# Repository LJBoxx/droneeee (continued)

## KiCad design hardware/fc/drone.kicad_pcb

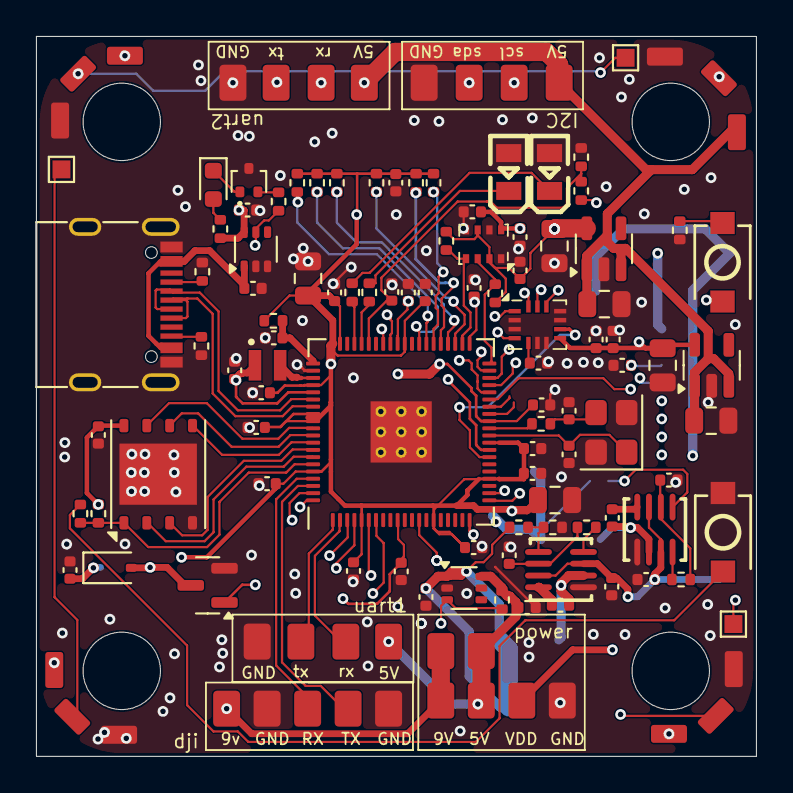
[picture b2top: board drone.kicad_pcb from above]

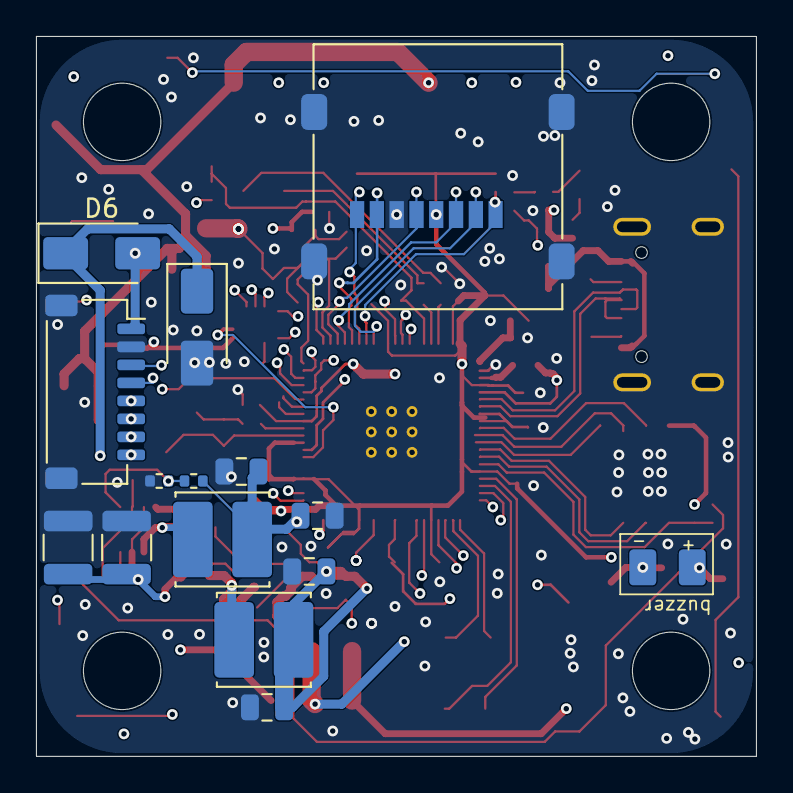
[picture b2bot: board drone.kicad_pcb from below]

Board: 4 copper layers, 40.0 x 40.0 mm, 137 parts (16 on the bottom side), 82 nets.

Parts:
C1, C4, C5, C6, C11, C12, C15, C16, C21, C22, C25, C26, C29, C35, C37, C38, C41, C42, C43, C45, C46, C49, C51: 100nf; C_0402_1005Metric
C2, C3, C7, C31: 4.7u; C_0402_1005Metric
C8, C17, C33: 100n; C_0402_1005Metric
C9, C10: 15p; C_0402_1005Metric
C13, C14, C23, C24: 1uf; C_0805_2012Metric
C18, C20, C30, C36: 22u; C_0805_2012Metric
C19, C34: 10u; C_1210_3225Metric
C27, C47: 2.2uf; C_0402_1005Metric
C28, C32, C39, C40: 1uf; C_0402_1005Metric
C44, C48: 10uf; C_0805_2012Metric
D1: C2297; LED0805-R-RD
D2: LED; LED_0603_1608Metric
D3: C2296; LED0805-R-RD
D4: D_Schottky; D_SOD-323
D6: D_Schottky; D_SMA
D8: SMAJ30A; D_SMA
J1, J3, J4, J5, J6, J7, J8, J9, J10, J11, J13, J14, J15, J16, J17, J18, J23, J24, J25, J26, J27, J28, J29: Conn_01x01; signal_pad
J2: Conn_01x08; JST_SH_SM08B-SRSS-TB_1x08-1MP_P1.00mm_Horizontal
J12: Micro_SD_Card; microSD_HC_Molex_47219-2001
J19, J20, J21, J22: Conn_01x03; led_ring
J30, J31, J32: Conn_01x01; TestPoint_Pad_1.0x1.0mm
L1, L2: 22uH; L_Cenker_CKCS5040
L3: 3.3u; L_pol_2016
Q1: AO3400A; SOT-23
Q2: NPN; SOT-416
R1, R2, R3, R4, R13, R20, R22, R23, R24, R27, R28, R29, R30: 10k; R_0402_1005Metric
R5, R7, R9, R10, R12: 100k; R_0402_1005Metric
R6, R14: 24.9k; R_0402_1005Metric
R8: 33r; R_0402_1005Metric
R11, R19, R21, R26: 1k; R_0402_1005Metric
R15, R16: 5.1k; R_0402_1005Metric
R25: 0; R_0402_1005Metric
SW1, SW2: SW_Push; SW-SMD_L3.9-W3.0-P4.45
TP1: BUZZER+; signal_pad
TP2: BUZZER-; signal_pad
U1, U7: MP9943GQ(TOKMAS); QFN-8_L3.0-W3.0-P0.65-BL
U2: TLV75533PDBV; SOT-23-5
U3: W25Q128JVP; WSON-8-1EP_6x5mm_P1.27mm_EP3.4x4.3mm
U4: RP2350_80QFN; RP2350-QFN-80-1EP_10x10_P0.4mm_EP3.4x3.4mm_ThermalVias
U5: ICM-42688-P; Bosch_LGA-14_3x2.5mm_P0.5mm
U6: LP5907MFX-3.3; SOT-23-5
U8: BMP280; Bosch_LGA-8_2x2.5mm_P0.65mm_ClockwisePinNumbering
U9, U10: LM66100DCK; SOT-363_SC-70-6
USB1: USB_C_Receptacle_USB2.0_14P; USB_C_Receptacle_G-Switch_GT-USB-7010ASV
Y1: ABM8-272-T3; Crystal_SMD_3225-4Pin_3.2x2.5mm

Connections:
+1V1: C2.1, C8.1, C11.2, C31.1, L3.1, U4.10 (DVDD), U4.32 (DVDD), U4.51 (DVDD), U4.65 (VREG_FB)
+5V: C14.1, C16.2, C23.2, C38.1, C41.1, D4.1 (K), J3.1 (Pin_1_1), J11.1 (Pin_1_1), J13.1 (Pin_1_1), J19.3, J20.3, J21.3, J22.3, J24.1 (Pin_1_1), J29.1 (Pin_1_1), R3.2, R11.1, TP1.1 (1_1), U2.1 (IN), U2.3 (EN), U6.1 (IN), U6.3 (EN), U9.6 (VOUT), U10.6 (VOUT)
+9V: C30.1, C36.1, J5.1 (Pin_1_1), J10.1 (Pin_1_1), J23.1 (Pin_1_1), L2.2, R9.2
/QSPI_SCLK: U3.6 (CLK), U4.71 (QSPI_SCLK)
/QSPI_SD0: U3.5 (DI/IO_{0}), U4.72 (QSPI_SD0)
/QSPI_SD1: U3.2 (DO/IO_{1}), U4.74 (QSPI_SD1)
/QSPI_SD2: U3.3 (~WP/IO_{2}), U4.73 (QSPI_SD2)
/QSPI_SD3: U3.7 (~HOLD/~RESET/IO_{3}), U4.70 (QSPI_SD3)
/QSPI_SS: R1.2, R25.2, U3.1 (~CS), U4.75 (QSPI_SS)
/VREG_AVDD: C3.1, R8.2, U4.61 (VREG_AVDD)
/VREG_LX: L3.2, U4.63 (VREG_LX)
/XIN: C10.1, U4.30 (XIN), Y1.1
/XOUT: R26.1, U4.31 (XOUT)
/~USB_BOOT: R1.1, SW1.2
BAT_CURR: C22.2, J2.3 (Current), U4.52 (GPIO41_ADC1)
BAT_POWER: D6.2 (A), J2.1 (Power), R12.2
BAT_POW_PROT: C17.2, C19.1, C33.2, C34.1, D6.1 (K), D8.1 (A1), U1.3 (EN), U1.7 (VIN), U7.3 (EN), U7.7 (VIN)
BAT_VOLTAGE: C21.1, R12.1, R13.2, U4.55 (GPIO44_ADC4)
CMD: J12.3 (CMD), R23.2, U4.44 (GPIO35)
DAT0: J12.7 (DAT0), R27.2, U4.45 (GPIO36)
DAT1: J12.8 (DAT1), R28.2, U4.46 (GPIO37)
DAT2: J12.1 (DAT2), R20.2, U4.47 (GPIO38)
DAT3: J12.2 (DAT3/CD), R22.2, U4.48 (GPIO39)
DJI_RX0: J16.1 (Pin_1_1), U4.77 (GPIO0)
DJI_TX0: J17.1 (Pin_1_1), U4.78 (GPIO1)
GND: C1.2, C2.2, C3.2, C4.2, C5.2, C6.2, C7.2, C8.2, C9.2, C10.2, C11.1, C12.2, C13.2, C14.2, C15.1, C16.1, C17.1, C18.2, C19.2, C20.2, C21.2, C22.1, C23.1, C24.1, C25.2, C26.2, C27.2, C28.2, C30.2, C31.2, C32.2, C33.1, C34.2, C36.2, C37.2, C38.2, C39.1, C40.2, C41.2, C42.2, C43.2, C44.2, C45.2, C46.2, C47.2, C48.2, C49.2, C51.2, D1.1 (K), D3.1 (K), D8.2 (A2), J1.1 (Pin_1_1), J2.2 (Ground), J4.1 (Pin_1_1), J12.6 (VSS), J12.9 (SHIELD), J14.1 (Pin_1_1), J15.1 (Pin_1_1), J18.1 (Pin_1_1), J19.1, J20.1, J21.1, J22.1, J28.1 (Pin_1_1), Q1.2 (S), Q2.3 (E), R2.1, R6.1, R13.1, R14.1, R15.2, R16.1, SW1.1, U1.5 (GND), U2.2 (GND), U3.4 (GND), U3.9 (EP), U4.62 (VREG_PGND), U4.81 (GND), U5.2 (RESV), U5.3 (RESV), U5.6 (GND), U5.7 (RESV), U5.10 (RESV), U5.11 (RESV), U6.2 (GND), U7.5 (GND), U8.1 (GND), U8.5 (SDO), U8.7 (GND), U9.2 (GND), U9.3 (~CE), U10.2 (GND), USB1.A1 (GND), USB1.A12 (GND), USB1.B1 (GND), USB1.B12 (GND), USB1.S1 (SHIELD), Y1.2, Y1.4
I2C1_SCL: J27.1 (Pin_1_1), U4.80 (GPIO3)
I2C1_SDA: J26.1 (Pin_1_1), U4.79 (GPIO2)
I2C_SCK: R30.1, U4.42 (GPIO33), U8.4 (SCK)
I2C_SDA: R29.1, U4.40 (GPIO32), U8.3 (SDI)
IMU_CLK: U4.38 (GPIO30), U5.13 (AP_SCL/AP_SCLK)
IMU_CLKIN: U4.27 (GPIO26), U5.9 (INT2/FSYNC/CLKIN)
IMU_CS: U4.37 (GPIO29), U5.12 (AP_CS)
IMU_INT: U4.28 (GPIO27), U5.4 (INT1/INT)
IMU_SDA: U4.39 (GPIO31), U5.14 (AP_SDA/AP_SDIO/AP_SDI)
IMU_SDO: U4.36 (GPIO28), U5.1 (AP_SDO/AP_AD0)
LED_1: J20.2, U4.13 (GPIO14)
LED_2: J21.2, J30.1 (Pin_1_1)
LED_3: J22.2, J31.1 (Pin_1_1)
LED_4: J19.2, J32.1 (Pin_1_1)
LIPO_5V: C18.1, C20.1, C40.1, L1.2, R5.2, U10.1 (VIN)
MOTOR_1: J2.5 (Motor_1), U4.3 (GPIO6)
MOTOR_2: J2.6 (Motor_2), U4.4 (GPIO7)
MOTOR_3: J2.7 (Motor_3), U4.6 (GPIO8)
MOTOR_4: J2.8 (Motor_4), U4.7 (GPIO9)
unnamed: C9.1, R26.2, Y1.3
unnamed: D1.2 (A), R21.1
unnamed: D2.2 (A), R11.2
unnamed: D2.1 (K), Q2.1 (C)
unnamed: D3.2 (A), R19.1
unnamed: D4.2 (A), Q1.3 (D), TP2.1 (1_1)
unnamed: Q2.2 (B), R4.2
unnamed: R2.2, SW2.1
unnamed: C29.1, U1.4 (BST)
unnamed: R5.1, R6.2, U1.1 (FB)
unnamed: R7.2, U1.8 (PG)
unnamed: C29.2, L1.1, U1.6 (SW)
unnamed: C28.1, R7.1, U1.2 (VCC)
unnamed: SW2.2, U4.35 (RUN)
unnamed: C35.1, U7.4 (BST)
unnamed: R9.1, R14.2, U7.1 (FB)
unnamed: R10.2, U7.8 (PG)
unnamed: C35.2, L2.1, U7.6 (SW)
unnamed: C32.1, R10.1, U7.2 (VCC)
unnamed: R3.1, R4.1, U9.5 (ST), U10.3 (~CE)
unnamed: R16.2, USB1.A5 (CC1)
unnamed: R15.1, USB1.B5 (CC2)
PIO_UART2_RX: J8.1 (Pin_1_1), U4.21 (GPIO21)
PIO_UART2_TX: J9.1 (Pin_1_1), U4.22 (GPIO22)
SD_CLK: J12.5 (CLK), R24.2, U4.43 (GPIO34)
TELEMETRY: J2.4 (Telemetry), U4.53 (GPIO42_ADC2)
USART1_RX: J6.1 (Pin_1_1), U4.2 (GPIO5)
USART1_TX: J7.1 (Pin_1_1), U4.1 (GPIO4)
USB_5V: C39.2, U9.1 (VIN), USB1.A4 (VBUS), USB1.A9 (VBUS), USB1.B4 (VBUS), USB1.B9 (VBUS)
USB_D+: U4.67 (USB_DP), USB1.A6 (D+), USB1.B6 (D+)
USB_D-: U4.66 (USB_DM), USB1.A7 (D-), USB1.B7 (D-)
VACC: C24.2, C25.1, C27.1, C46.1, C47.1, U5.8 (VDD), U6.5 (OUT), U8.8 (VDD)
VCC: C26.1, U5.5 (VDDIO)
VDD: C1.1, C4.1, C5.1, C6.1, C7.1, C12.1, C13.1, C15.2, C37.1, C42.1, C43.1, C44.1, C45.1, C48.1, C49.1, C51.1, J12.4 (VDD), J25.1 (Pin_1_1), R8.1, R20.1, R22.1, R23.1, R24.1, R25.1, R27.1, R28.1, R29.2, R30.2, U2.5 (OUT), U3.8 (VCC), U4.5 (IOVDD), U4.15 (IOVDD), U4.24 (IOVDD), U4.29 (IOVDD), U4.41 (IOVDD), U4.50 (IOVDD), U4.59 (ADC_AVDD), U4.60 (IOVDD), U4.64 (VREG_VIN), U4.68 (USB_OTP_VDD), U4.69 (QSPI_IOVDD), U4.76 (IOVDD), U8.2 (CSB), U8.6 (VDDIO)
buzz: Q1.1 (G), U4.20 (GPIO20)
green_led: R21.2, U4.56 (GPIO45_ADC5)
yellow_led: R19.2, U4.57 (GPIO46_ADC6)

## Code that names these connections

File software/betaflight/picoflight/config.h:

/*
 * This file is part of Betaflight.
 *
 * Betaflight is free software. You can redistribute this software
 * and/or modify this software under the terms of the GNU General
 * Public License as published by the Free Software Foundation,
 * either version 3 of the License, or (at your option) any later
 * version.
 *
 * Betaflight is distributed in the hope that it will be useful,
 * but WITHOUT ANY WARRANTY; without even the implied warranty of
 * MERCHANTABILITY or FITNESS FOR A PARTICULAR PURPOSE.
 *
 * See the GNU General Public License for more details.
 *
 * You should have received a copy of the GNU General Public
 * License along with this software.
 *
 * If not, see <http://www.gnu.org/licenses/>.
 * 
 * This file was copied from MADFLIGHT_FC3 config and edited to match with picoflight pinout
 */

#pragma once

#define FC_TARGET_MCU        RP2350B
#define BOARD_NAME           picoflight
#define MANUFACTURER_ID      pota //to

// Board info: https://madflight.com/Board-FC3/

// For debugging (trace) via UART, make with env var PICO_TRACE set (see RP2350.mk).
// Example instance and pins below.
//#define PICO_TRACE_UART_INSTANCE  0
//#define PICO_TRACE_TX_GPIO        20
//#define PICO_TRACE_RX_GPIO        21

//------------------
// Internal Pins
//------------------

// Bus for internal I2C sensors
// NOTE: Board has BMP580 barometer, MMC5603 compass and INA226 power sensor. Sensors not supported by betaflight_2025.12.0-beta
#define I2C0_SCL_PIN         PA33
#define I2C0_SDA_PIN         PA32

//bmp280 barometer
#define USE_BARO_BMP280
#define BARO_I2C_INSTANCE            I2C0

// LED
#define LED0_PIN             PA45 // blue
//#define LED0_INVERTED

// Battery voltage
#define USE_ADC
#define ADC_INSTANCE         ADC1
#define ADC_VBAT_PIN         PA44
#define DEFAULT_VOLTAGE_METER_SOURCE   VOLTAGE_METER_ADC
#define DEFAULT_VOLTAGE_METER_SCALE    110 // 100k/10k divider

// RGB LED
#define LED_STRIP_PIN        PA14

// Gyro+acc
#define USE_GYRO_CLKIN
#define USE_GYRO
#define USE_GYRO_SPI_ICM42688P
#define USE_ACC
#define USE_ACC_SPI_ICM42688P
#define USE_ACCGYRO_ICM45686
#define USE_ACCGYRO_LSM6DSO
#define USE_ACCGYRO_LSM6DSV16X
#define USE_SPI_DEVICE_1
#define SPI1_SCK_PIN         PA30
#define SPI1_SDI_PIN         PA28
#define SPI1_SDO_PIN         PA31
#define GYRO_1_EXTI_PIN      PA27
#define GYRO_1_CS_PIN        PA29
#define GYRO_1_CLKIN_PIN     PA26  // for ICM42688P,ICP45686 needs #define USE_GYRO_CLKIN
#define GYRO_1_SPI_INSTANCE  SPI1
#define GYRO_1_ALIGN         CW180_DEG

// SDCARD 1-bit SPI - works
#define USE_SDCARD
#define USE_SDCARD_SPI
#define SPI0_SCK_PIN         PA34
#define SPI0_SDI_PIN         PA36
#define SPI0_SDO_PIN         PA35
#define SDCARD_SPI_CS_PIN    PA39
#define SDCARD_DETECT_PIN    NONE
#define SDCARD_DETECT_INVERTED
#define SDCARD_SPI_INSTANCE  SPI0
#define DEFAULT_BLACKBOX_DEVICE        BLACKBOX_DEVICE_SDCARD

/*
// SDCARD 4-bit SDIO - TODO - Compiles but still have "SD-CARD: Not configured" in configurator with betaflight_2025.12.0-beta
#define USE_SDCARD
#define SDCARD_DETECT_PIN    NONE
#define SDIO_DEVICE          SDIODEV_1
#define SDIO_USE_4BIT        1
#define SDIO_CK_PIN          PA34
#define SDIO_CMD_PIN         PA35
#define SDIO_D0_PIN          PA36
#define SDIO_D1_PIN          PA37
#define SDIO_D2_PIN          PA38
#define SDIO_D3_PIN          PA39
#define DEFAULT_BLACKBOX_DEVICE        BLACKBOX_DEVICE_SDCARD
*/

//------------------
// External Pins
//------------------

// Board has 3 rows of 10 external GPIOS, each row has 3 power+ground pins. Available pins are PA0-25,40-43

// --- First row of pins ---

// RC Radio - 1-on-1 connect ELRS / CRSF module
#define UART0_TX_PIN         PA0
#define UART0_RX_PIN         PA1
//+5V
//GND

// GPS + Compass
#define I2C1_SDA_PIN         PA2
#define I2C1_SCL_PIN         PA3
#define UART1_TX_PIN         PA4
#define UART1_RX_PIN         PA5
//+5V
//GND

// Motors
#define MOTOR1_PIN           PA6 // pwm3a
#define MOTOR2_PIN           PA7 // pwm3b
#define MOTOR3_PIN           PA8 // pwm4a
#define MOTOR4_PIN           PA9 // pwm4b
//+3.3V
//GND

#define BEEPER_PIN           PA20

// --- Second row of pins ---

// Additional UART
#define PIOUART0_TX_PIN      PA21
#define PIOUART0_RX_PIN      PA22
//+5V
//GND

// External LEDs
//#define LED1_PIN             PA12 // green
//#define LED1_INVERTED
//#define LED2_PIN             PA13 // red
//#define LED2_INVERTED

// Additional UART
//#define PIOUART1_TX_PIN      PA14
//#define PIOUART1_RX_PIN      PA15
//+5V
//GND

// Additional motors
//#define MOTOR5_PIN           PA16 // pwm0a
//#define MOTOR6_PIN           PA17 // pwm0b
//#define MOTOR7_PIN           PA18 // pwm1a
//#define MOTOR8_PIN           PA19 // pwm1b
//+3.3V
//GND

// --- Third row of pins ---

// Debugging (trace) via UART
//PA20 used as PICO_TRACE_TX_GPIO
//PA21 used as PICO_TRACE_RX_GPIO
//+5V
//GND

// GPIOs
//#define PINIO1_PIN PA22
//#define PINIO2_PIN PA23
//#define PINIO3_PIN PA24
//#define PINIO4_PIN PA25
//+5V
//GND

// ADC pins
//#define ADC_RSSI_PIN         PA40
//#define ADC_CURR_PIN         PA41 //with this stack curr pin is replaced with telemrx
#define ADC_EXTERNAL1_PIN    PA42
//PA43 unused
//+3.3V
//GND

// Optional external barometer connected to I2C1 (second i2c bus) PA2=SDA PA3=SCL
#define USE_BARO
#define USE_BARO_MS5611
#define USE_BARO_BMP280
#define USE_BARO_BMP388
#define USE_BARO_LPS
#define USE_BARO_QMP6988
#define USE_BARO_DPS310
#define USE_BARO_BMP085
#define USE_BARO_2SMBP_02B
#define USE_BARO_LPS22DF
#define BARO_I2C_INSTANCE    I2CDEV_1

// Optional external compass connected to I2C1 (second i2c bus) PA2=SDA PA3=SCL
#define USE_MAG
#define USE_MAG_HMC5883
#define USE_MAG_QMC5883
#define USE_MAG_LIS2MDL
#define USE_MAG_LIS3MDL
#define USE_MAG_AK8975
#define USE_MAG_IST8310
#define MAG_I2C_INSTANCE     I2CDEV_1

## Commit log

2025-12-30 pcb update
2025-12-30 commit
    +gitignore
    +esc schematic
2025-12-31 update sch
    fixed wrong mcu package
    + i suppose gitignore doing its thing
2026-01-01 push
2026-01-02 finished routinnnn
    :3
2026-04-29 poush up to date
    its been a long time since i last pushed but some updates were on the way
2026-06-24 reorg+ fixes
2026-06-24 uh img fix ?
2026-06-26 zine fix !
